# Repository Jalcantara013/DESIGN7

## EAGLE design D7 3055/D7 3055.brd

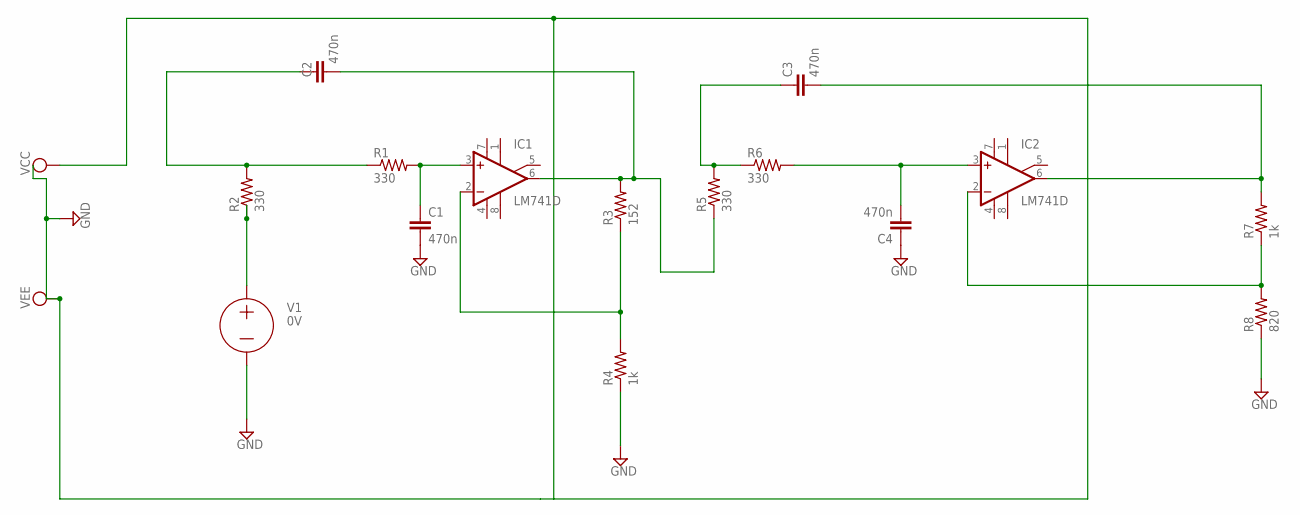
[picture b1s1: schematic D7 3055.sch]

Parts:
C1, C2, C3, C4: 470n; C2.5-3
IC1, IC2: LM741D; SO08
R1, R2, R5, R6: 330; 0204/7
R3: 152; 0204/7
R4, R7: 1k; 0204/7
R8: 820; 0204/7

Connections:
GND: C1.2, C4.1, R4.1, R8.1
unnamed: C2.1, R1.1, R2.2
unnamed: C1.1, IC1.3 (+IN), R1.2
unnamed: C3.1, R5.2, R6.1
unnamed: C2.2, IC1.6 (OUT), R3.2, R5.1
unnamed: IC1.2 (-IN), R3.1, R4.2
unnamed: C3.2, IC2.6 (OUT), R7.2
unnamed: C4.2, IC2.3 (+IN), R6.2
unnamed: IC2.2 (-IN), R7.1, R8.2
V+: IC1.7 (V+), IC2.7 (V+)
V-: IC1.4 (V-), IC2.4 (V-)

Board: 2 copper layers, 14 parts (0 on the bottom side), 11 nets, no tracks yet.
